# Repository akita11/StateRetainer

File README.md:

# StateRetainer

Grove端子のデジタル信号の変化を、マイコン等で扱いやすいように「保持」するものです。スイッチを短い時間押す、などの単発信号をとらえ、一定時間、またはリセットを書けるまで、出力にその値を保持します。

内部的は、いわゆる"555"をそのまま使っています。（参考：[555の動作](https://www.marutsu.co.jp/contents/shop/marutsu/mame/166.html)）

## ピン配置

- Grove（In側）: IN/x/VDD/GND ※INは入力（プルアップ）
- Grove（Out側）: OUT/RST/VDD/GND ※OUTは出力、RSTは入力（プルダウン）

OUT=1の時には、LEDが点灯し、出力の状態を確認できます。

※内部の回路(555)はGrove端子から供給される電源電圧で動作するため、RST入力を"1"とするには、電源電圧の2/3以上の電圧が必要です。またOUT出力の"1"の電圧も電源電圧となります。M5StackシリーズではVDDは5VですがIO電圧は3.3Vのため、RSTはぎりぎり"1"に足りません（個体差で"1"と判別される場合もあります）。またOUTの"1"は5Vのため、IOピンの入力電圧の範囲を超えます。そのため、確実な動作のためには、Grove端子の電源電圧として3.3Vを供給してください（[こちら](https://www.switch-science.com/products/9461)を使うとGroveケーブルの中継としてはさむことで3.3Vを生成して供給できます）

## 動作

目的にあわせて、以下の3通りの動作状態を設定できます。

### 保持動作（デフォルト状態）

INの状態変化を出力に保持します。いわゆるRSフリップフロップとしての動作です。なおINは内部でプルアップ、RSTはプルダウンされているので、IN、RSTの開放時には、それぞれ"1"、"0"と同等です（待機状態）。

- INが1→0になると、OUT=1となり、その状態を保持。
- その状態で、RSTを0→1とすると、OUT=0に復帰。

【構成】: C1/C2、R1/R3、R2/R4に部品を取り付けなず、JP1/JP2を開放（初期状態）

### 単発パルス発生動作

INが1→0になると、指定時間（T=1.1*CR[s]）間のみ、OUT=1となり、その後、OUT=1に復帰します。

- 【構成】: R7を除去し、C1/C2にコンデンサC、R1/R3に抵抗Rを接続し、R2/R4は抵抗を取り付けず、JP1を短絡、JP2を開放

### 発振動作

入力に関係なく、f=1.44 / (Ra + 2*Rb)C [Hz]で発振します。

- 【構成】: R6, R7を除去し、R1/R3にRa、R2/R4にRb、C1/C2にCを接続し、JP2を短絡、JP1を開放

## 出力の極性の切り替え

出力OUTはJP3によって、正論理（デフォルト、OFF時=0、ON時=1）・負論理（オープンコレクタ、OFF時=開放、ON時=0）を切り替えできます。負論理の場合は保持動作時にはR1/R3にプルアップ抵抗を取り付け可能。上記のOUTの値の表記は正論理時の値の表記です。

## Author

Junichi Akita (akita@ifdl.jp, @akita11)

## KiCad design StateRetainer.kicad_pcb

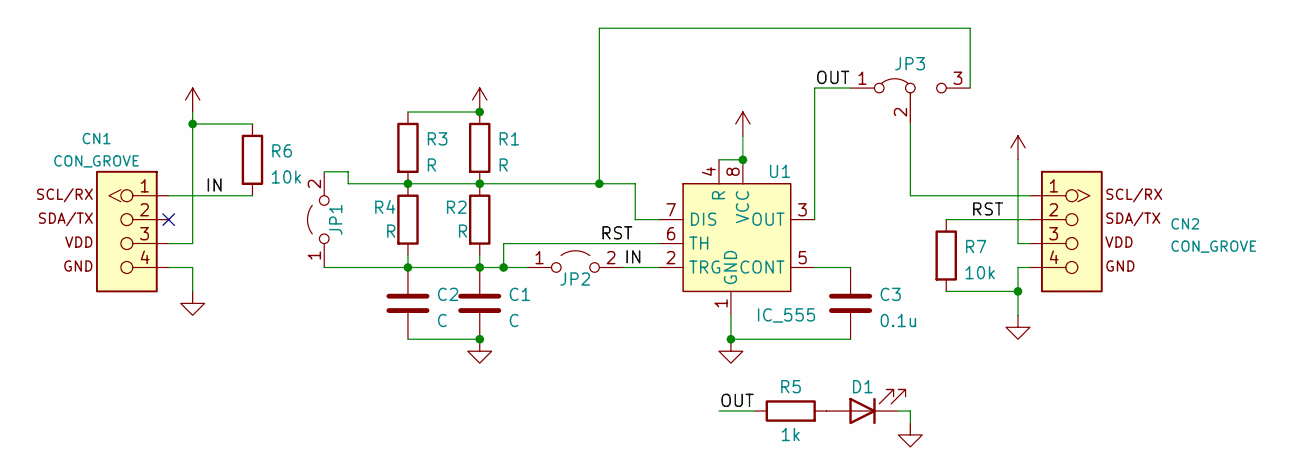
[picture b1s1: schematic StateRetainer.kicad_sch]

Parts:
C1: C; C_0603_1608Metric
C2: C; C_Disc_D3.0mm_W2.0mm_P2.50mm
C3: 0.1u; C_0603_1608Metric
CN1, CN2: CON_GROVE; CON_GROVE_H
D1: LED; C_0603_1608Metric
JP1, JP2: Jumper_2_Open; SolderJumper-2_P1.3mm_Open_Pad1.0x1.5mm
JP3: Jumper_3_Bridged12; SolderJumper-3_P1.3mm_Bridged2Bar12_Pad1.0x1.5mm
R1, R2: R; R_0603_1608Metric
R3, R4: R; R_Axial_DIN0207_L6.3mm_D2.5mm_P2.54mm_Vertical
R5: 1k; R_0603_1608Metric
R6, R7: 10k; R_0603_1608Metric
U1: IC_555; SOIC-8_5.23x5.23mm_P1.27mm

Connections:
/IN: CN1.1, JP2.2 (B), R6.2, U1.2 (TRG)
/OUT: JP3.1 (A), R5.1, U1.3 (OUT)
/RST: C1.1, C2.1, CN2.2, JP1.1 (A), JP2.1 (A), R2.2, R4.2, R7.1, U1.6 (TH)
GND: C1.2, C2.2, C3.2, CN1.4, CN2.4, D1.1 (K), R7.2, U1.1 (GND)
unnamed: C3.1, U1.5 (CONT)
unnamed: CN2.1, JP3.2 (C)
unnamed: D1.2 (A), R5.2
unnamed: JP1.2 (B), JP3.3 (B), R1.2, R2.1, R3.2, R4.1, U1.7 (DIS)
VCC: CN1.3, CN2.3, R1.1, R3.1, R6.1, U1.4 (R), U1.8 (VCC)

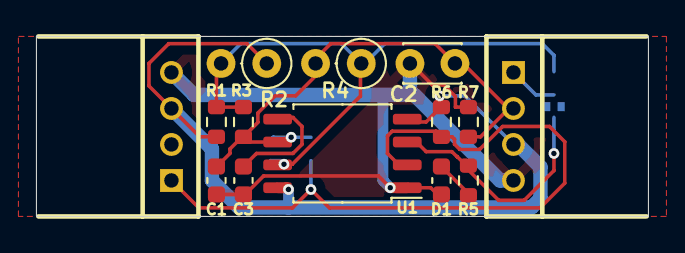
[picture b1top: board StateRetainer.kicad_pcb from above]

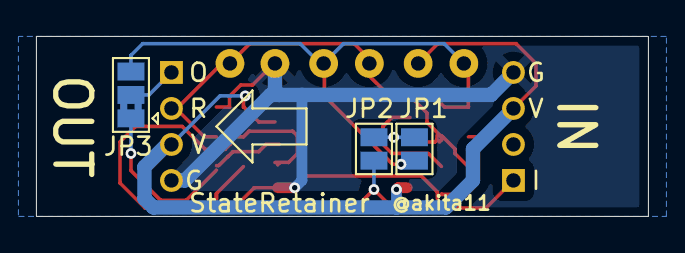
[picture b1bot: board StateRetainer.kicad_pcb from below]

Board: 2 copper layers, 34.0 x 10.0 mm, 17 parts (3 on the bottom side), 9 nets.

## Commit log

2023-12-13 update README, add photos
